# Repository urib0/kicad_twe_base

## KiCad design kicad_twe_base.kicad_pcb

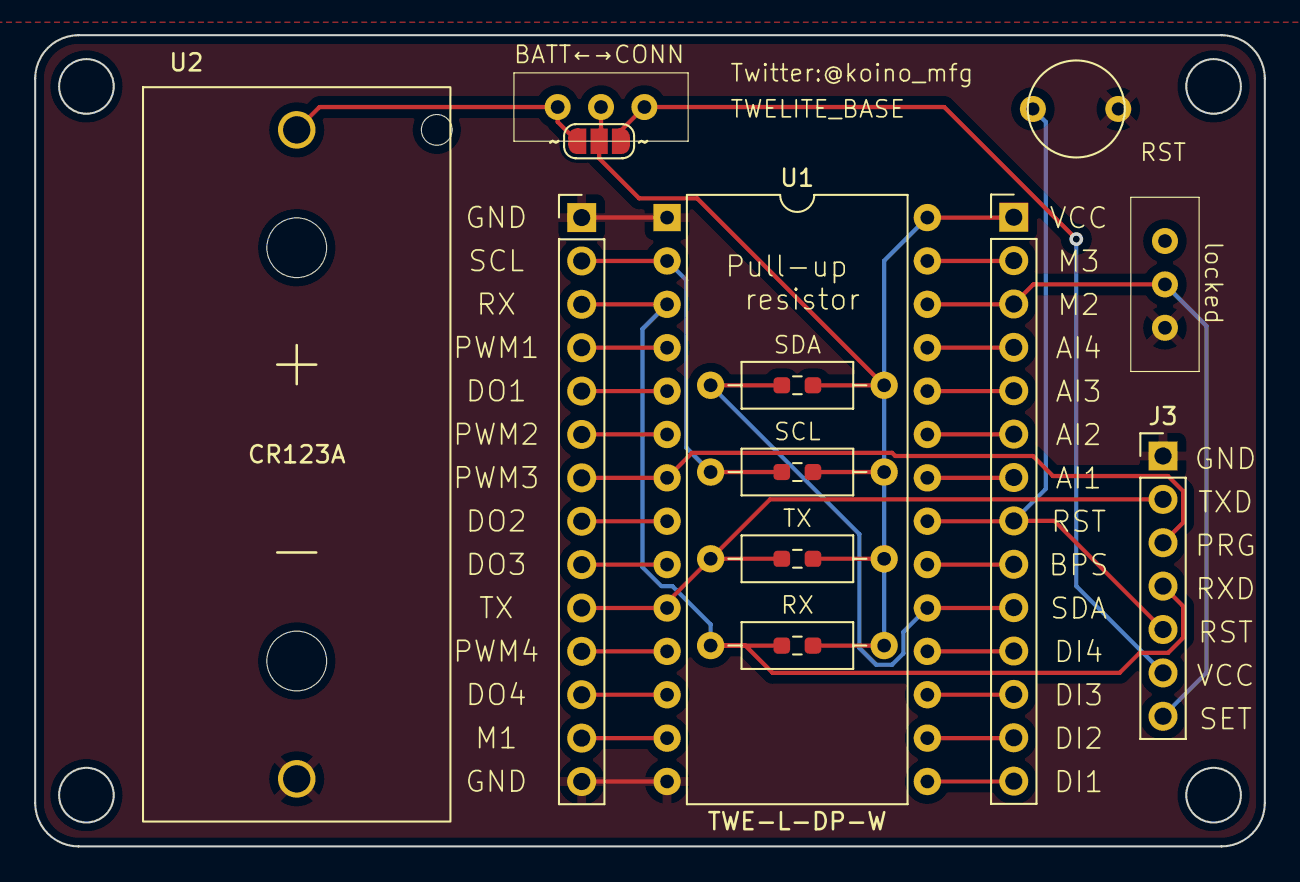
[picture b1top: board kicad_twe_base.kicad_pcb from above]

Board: 2 copper layers, 72.0 x 47.5 mm, 10 parts (0 on the bottom side), 11 nets.

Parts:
BATT←→CONN: SW_SLIDE_sengoku
J3: PinHeader_1x07_P2.54mm_Vertical
RST: SW_PUSH_2pin
RX: R_Axial_DIN0207_L6.3mm_D2.5mm_P10.16mm_Horizontal
SCL: R_Axial_DIN0207_L6.3mm_D2.5mm_P10.16mm_Horizontal
SDA: R_Axial_DIN0207_L6.3mm_D2.5mm_P10.16mm_Horizontal
TX: R_Axial_DIN0207_L6.3mm_D2.5mm_P10.16mm_Horizontal
U1: TWE-L-DP-W; DIP-28_W15.24mm
U2: BHC-CR123A
locked: SW_SLIDE_sengoku

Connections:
+3V3: BATT←→CONN.2 (B), RX.2, SCL.2, SDA.2, TX.2, U1.28 (VCC)
GND: J3.1, RST.2, U1.1 (GND), U1.14 (GND), U2.2 (-), locked.3 (C)
unnamed: SCL.1, U1.2 (DIO14/SCL)
unnamed: J3.4, RX.1, U1.3 (DIO7/RX)
unnamed: J3.3, U1.7 (DO1/PWM3)
unnamed: J3.2, TX.1, U1.10 (DIO6/TX)
unnamed: J3.7, U1.26 (DIO2/M2), locked.2 (B)
unnamed: J3.5, RST.1, U1.21 (~RESET)
unnamed: SDA.1, U1.19 (DIO15/SDA)
unnamed: BATT←→CONN.3 (C), J3.6
unnamed: BATT←→CONN.1 (A), U2.1 (+)

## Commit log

2022-01-07 TWELITEの配置配線済み
2022-01-07 TWELITE周辺の配線を修正
2022-01-10 TWELITE R2用の書き込み端子を用意した
2022-01-10 ガーバー、バックアップファイルの追加
2022-01-10 配線完了 ERC NG
2022-01-10 3v3,GNDのPWR_FLGを削除
2022-01-12 123Aのバッテリーホルダを追加
2022-01-12 123Aのバッテリーホルダを削除
2022-01-12 シルク変更途中
2022-01-12 仮配置完了
2022-01-12 リセットSWとPRG SWをGNDに落とし忘れていた
2022-01-13 VCCとGNDのPWR_FLAGをつけた
2022-01-13 TWELITEのシンボルの電源をPower Inputに変更した
2022-01-13 UART,I2Cのプルアップ抵抗を追加
2022-01-13 プルアップ抵抗抵抗仮配置
2022-01-13 シルク修正
2022-01-13 配線完了 DRC OK
2022-01-13 ガーバー出力とドリル出力の設定をPCBWay向けに変更
2022-01-13 署名等を入れた
